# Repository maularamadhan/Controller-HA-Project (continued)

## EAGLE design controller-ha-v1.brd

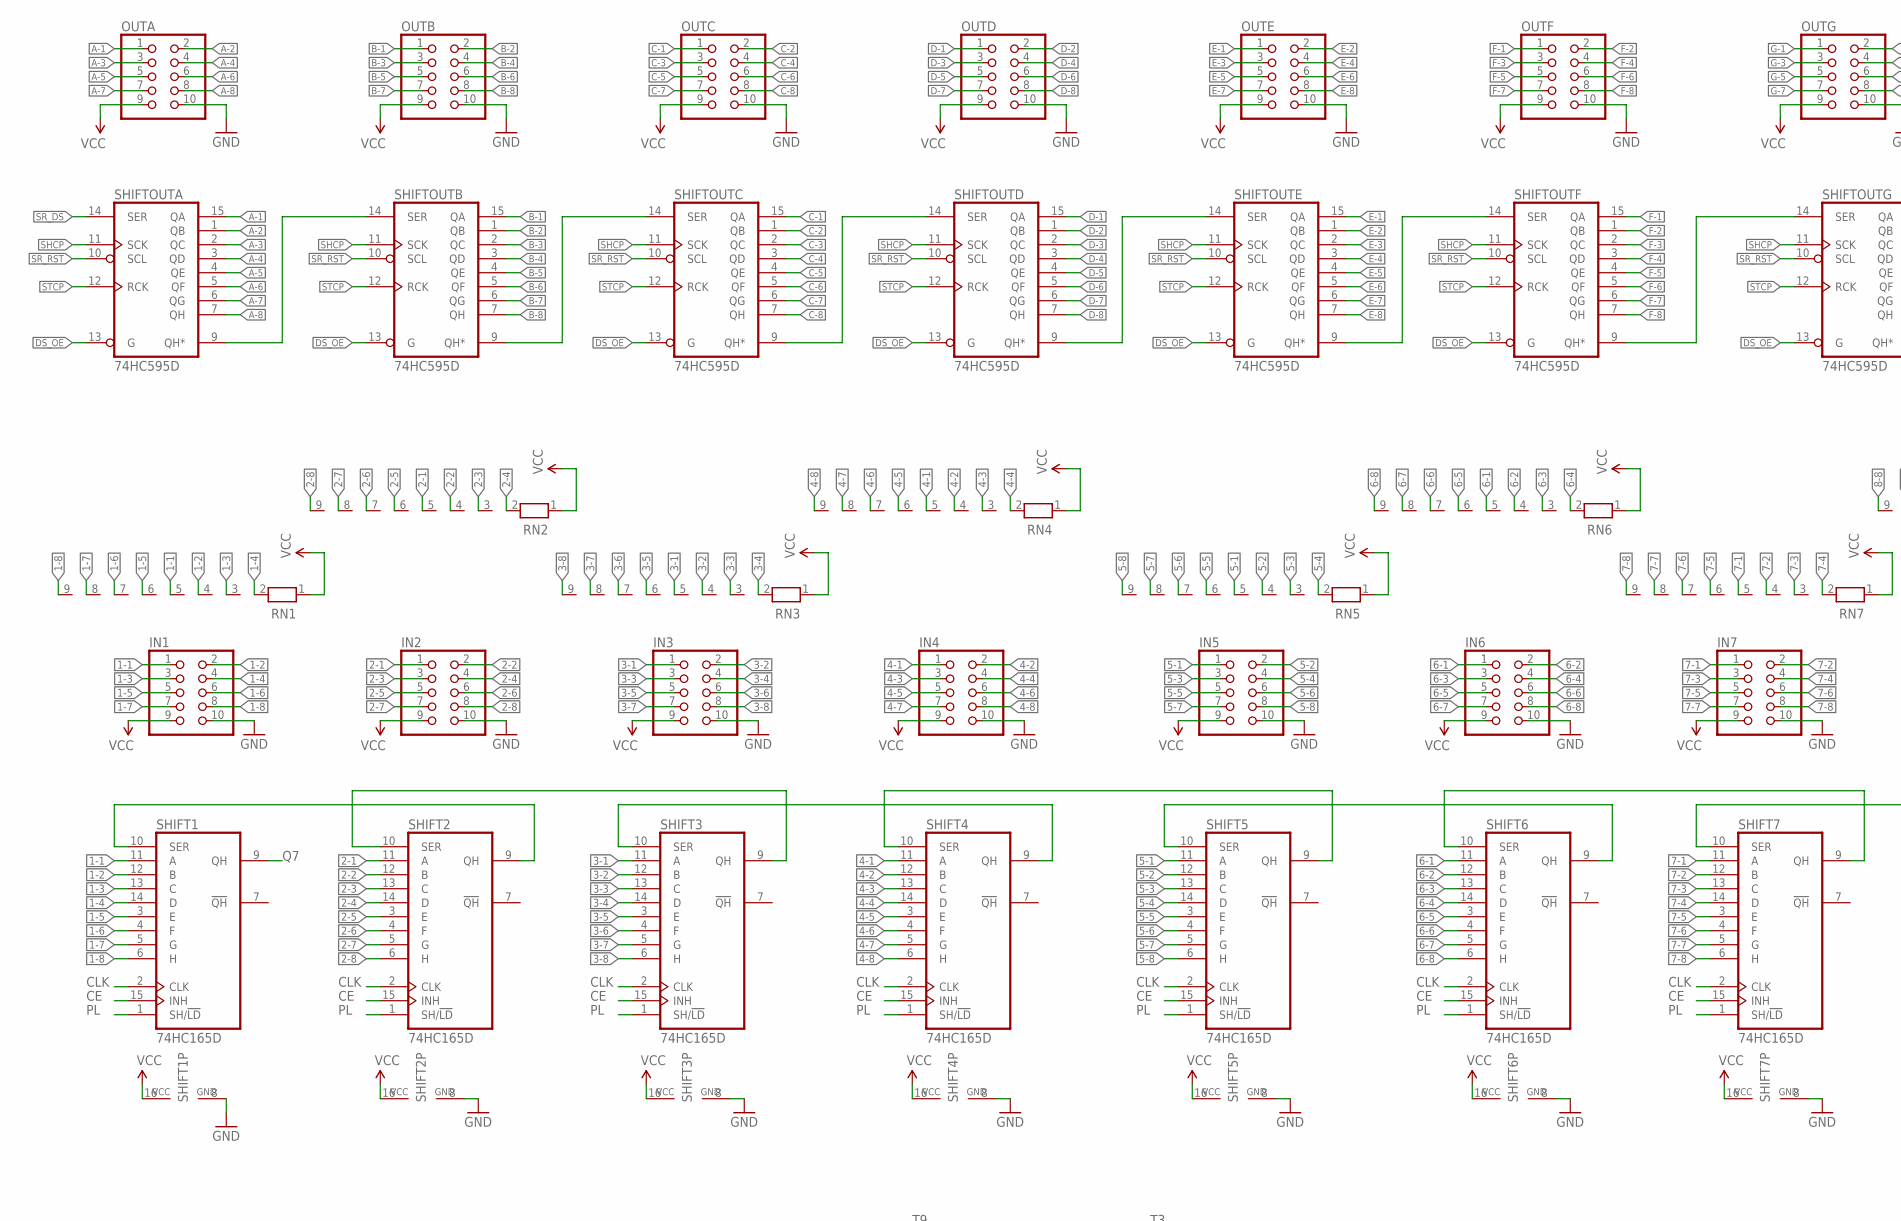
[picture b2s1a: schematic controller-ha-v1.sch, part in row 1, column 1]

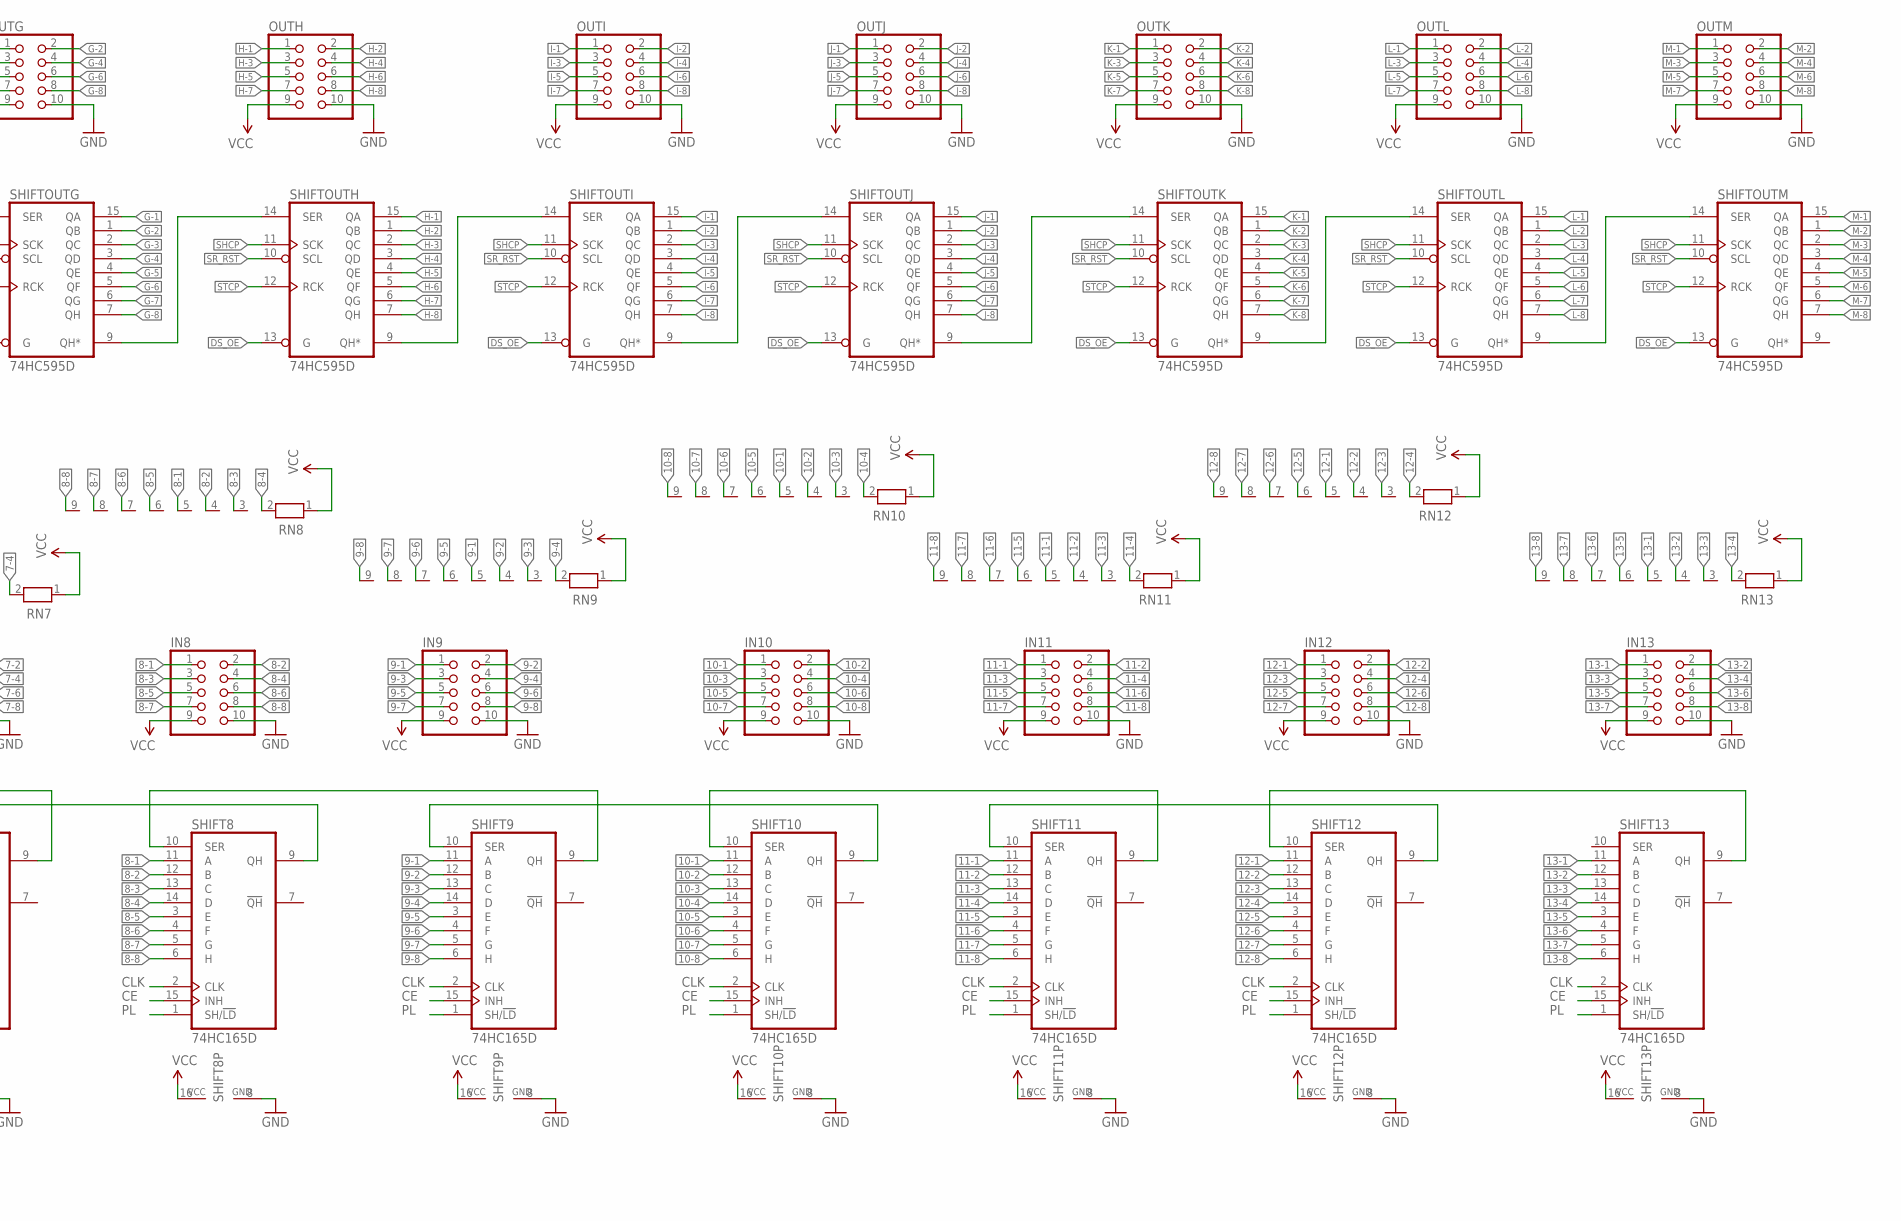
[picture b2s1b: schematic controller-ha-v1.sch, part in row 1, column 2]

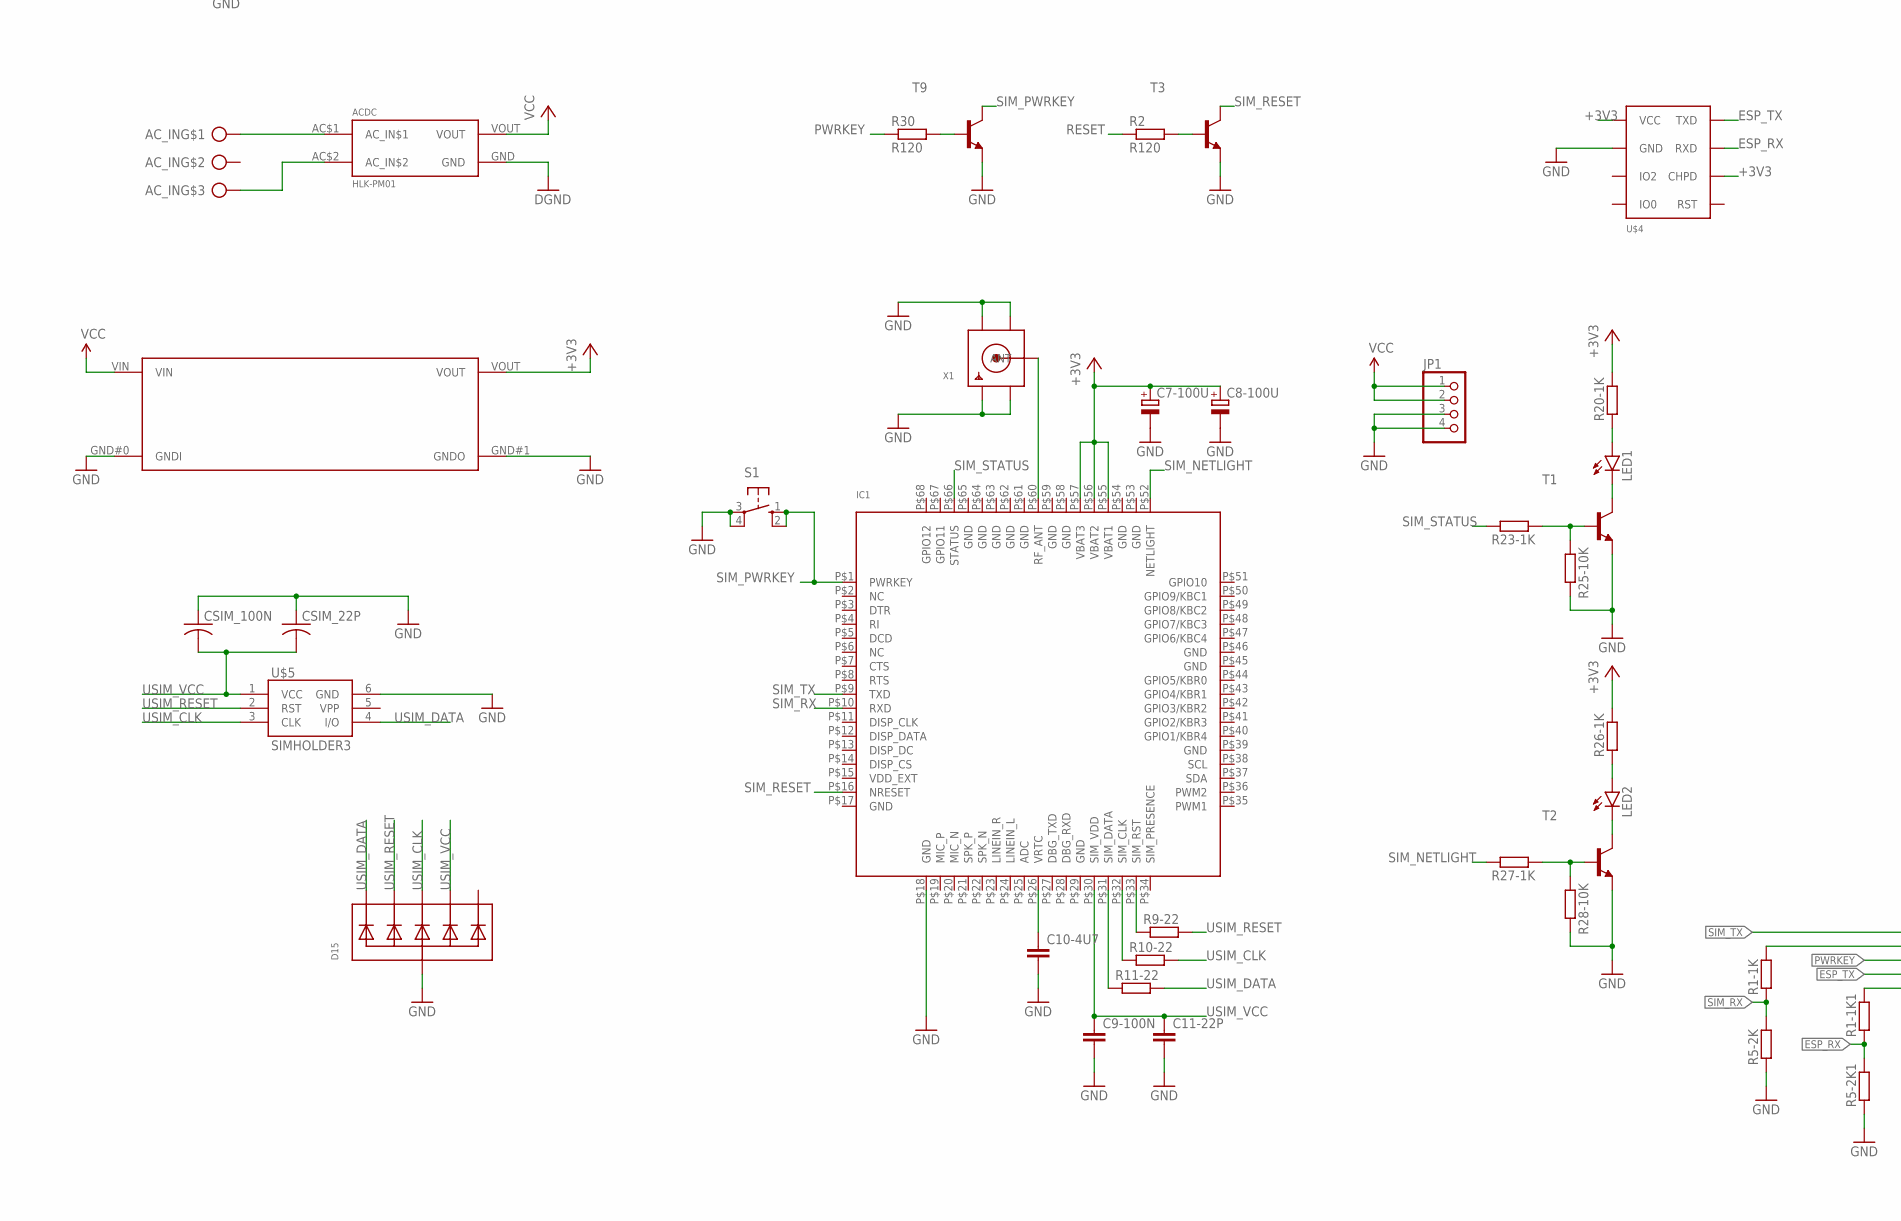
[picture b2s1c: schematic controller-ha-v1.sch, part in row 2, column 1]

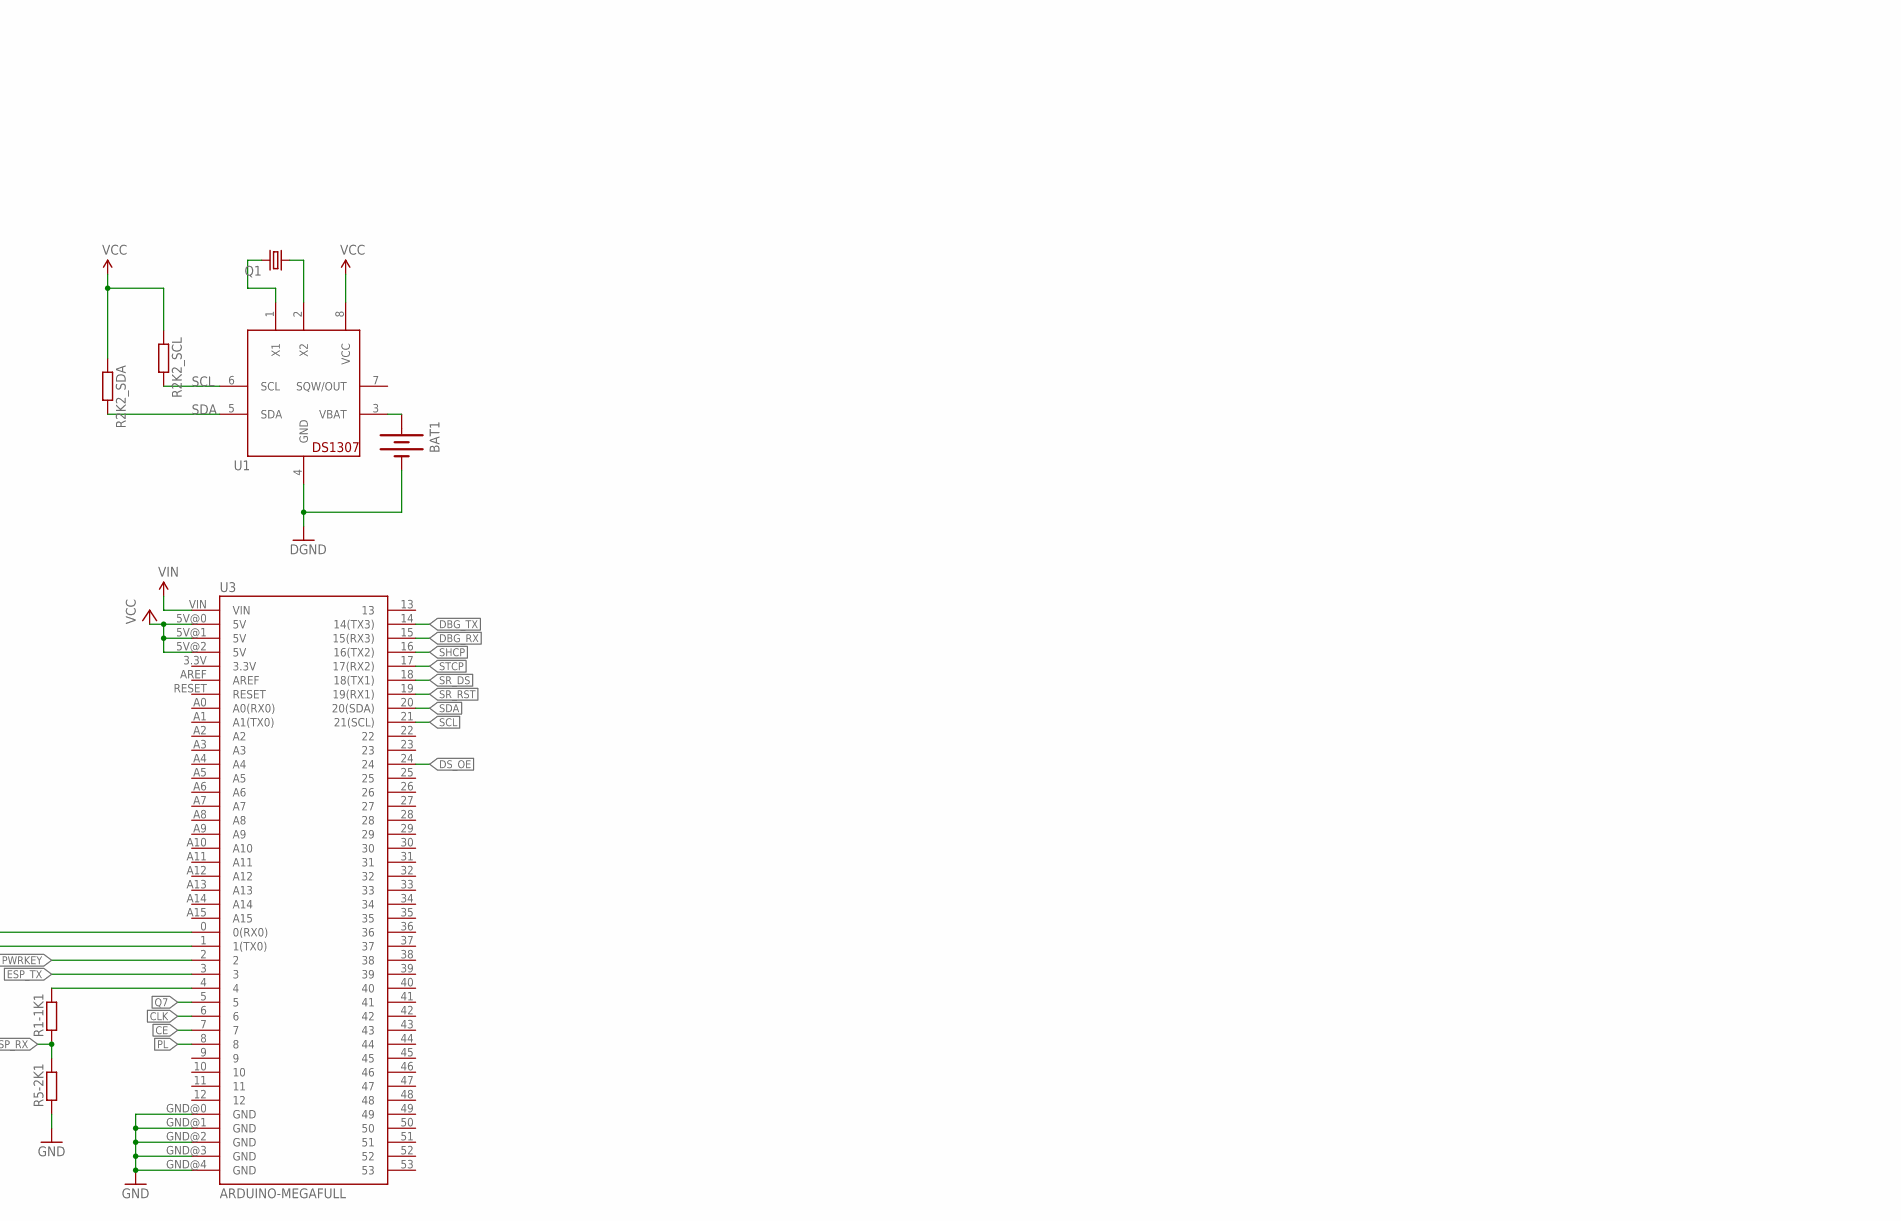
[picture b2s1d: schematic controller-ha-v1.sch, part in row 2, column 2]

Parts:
ACDC: HLK-PM01
AC_IN: AK3003
BAT1: BATTERY20PTH; BATTCOM_20MM_PTH
C7-100U, C8-100U: CPOL-EU153CLV-0605; 153CLV-0605
C9-100N, C10-4U7, C11-22P: C-EUC0603; C0603
CSIM_22P, CSIM_100N: C-USC0603K; C0603K
D15: TVSARRAY_5LANE; SOT363
IC1: GSM_SIM900_LITERAL; SIM900_SMT
IN1, IN2, IN3, IN4, IN5, IN6, IN7, IN8, IN9, IN10, IN11, IN12, IN13: PINHD-2X5; 2X05
JP1: PINHD-1X4; 1X04
LED1, LED2: LED-3MM-NO_SILK; LED3MM-NS
OUTA: PINHD-2X5; 2X05
OUTB: PINHD-2X5; 2X05
OUTC: PINHD-2X5; 2X05
OUTD: PINHD-2X5; 2X05
OUTE: PINHD-2X5; 2X05
OUTF: PINHD-2X5; 2X05
OUTG: PINHD-2X5; 2X05
OUTH: PINHD-2X5; 2X05
OUTI: PINHD-2X5; 2X05
OUTJ: PINHD-2X5; 2X05
OUTK: PINHD-2X5; 2X05
OUTL: PINHD-2X5; 2X05
OUTM: PINHD-2X5; 2X05
Q1: CRYSTALTC26H; TC26H
R1-1K, R1-1K1, R2K2_SCL, R2K2_SDA, R5-2K, R5-2K1, R9-22, R10-22, R11-22, R20-1K, R23-1K, R25-10K, R26-1K, R27-1K, R28-10K: R-EU_R0603; R0603
R2, R30: R120; M0805
RN1, RN2, RN3, RN4, RN5, RN6, RN7, RN8, RN9, RN10, RN11, RN12, RN13: RN08; RN-9
S1: 10-XX; B3F-10XX
SHIFT1, SHIFT2, SHIFT3, SHIFT4, SHIFT5, SHIFT6, SHIFT7, SHIFT8, SHIFT9, SHIFT10, SHIFT11, SHIFT12, SHIFT13: 74HC165D; SO16
SHIFTOUTA: 74HC595D; SO16
SHIFTOUTB: 74HC595D; SO16
SHIFTOUTC: 74HC595D; SO16
SHIFTOUTD: 74HC595D; SO16
SHIFTOUTE: 74HC595D; SO16
SHIFTOUTF: 74HC595D; SO16
SHIFTOUTG: 74HC595D; SO16
SHIFTOUTH: 74HC595D; SO16
SHIFTOUTI: 74HC595D; SO16
SHIFTOUTJ: 74HC595D; SO16
SHIFTOUTK: 74HC595D; SO16
SHIFTOUTL: 74HC595D; SO16
SHIFTOUTM: 74HC595D; SO16
T1, T2, T3, T9: MMBT2222ALT1-NPN-SOT23-BEC; SOT23-BEC
U1: DS1307; DIL08
U3: ARDUINO-MEGAFULL; ARDUINO_MEGA
U$2: DCDCMODULE
U$4: ESP8266
U$5: SIMHOLDER3
X1: SMACONNECTOR; SMA90_DIP

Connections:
1-1: IN1.1, RN1.5, SHIFT1.11 (A)
1-2: IN1.2, RN1.4, SHIFT1.12 (B)
1-3: IN1.3, RN1.3, SHIFT1.13 (C)
1-4: IN1.4, RN1.2, SHIFT1.14 (D)
1-5: IN1.5, RN1.6, SHIFT1.3 (E)
1-6: IN1.6, RN1.7, SHIFT1.4 (F)
1-7: IN1.7, RN1.8, SHIFT1.5 (G)
1-8: IN1.8, RN1.9, SHIFT1.6 (H)
2-1: IN2.1, RN2.5, SHIFT2.11 (A)
2-2: IN2.2, RN2.4, SHIFT2.12 (B)
2-3: IN2.3, RN2.3, SHIFT2.13 (C)
2-4: IN2.4, RN2.2, SHIFT2.14 (D)
2-5: IN2.5, RN2.6, SHIFT2.3 (E)
2-6: IN2.6, RN2.7, SHIFT2.4 (F)
2-7: IN2.7, RN2.8, SHIFT2.5 (G)
2-8: IN2.8, RN2.9, SHIFT2.6 (H)
3-1: IN3.1, RN3.5, SHIFT3.11 (A)
3-2: IN3.2, RN3.4, SHIFT3.12 (B)
3-3: IN3.3, RN3.3, SHIFT3.13 (C)
3-4: IN3.4, RN3.2, SHIFT3.14 (D)
3-5: IN3.5, RN3.6, SHIFT3.3 (E)
3-6: IN3.6, RN3.7, SHIFT3.4 (F)
3-7: IN3.7, RN3.8, SHIFT3.5 (G)
3-8: IN3.8, RN3.9, SHIFT3.6 (H)
4-1: IN4.1, RN4.5, SHIFT4.11 (A)
4-2: IN4.2, RN4.4, SHIFT4.12 (B)
4-3: IN4.3, RN4.3, SHIFT4.13 (C)
4-4: IN4.4, RN4.2, SHIFT4.14 (D)
4-5: IN4.5, RN4.6, SHIFT4.3 (E)
4-6: IN4.6, RN4.7, SHIFT4.4 (F)
4-7: IN4.7, RN4.8, SHIFT4.5 (G)
4-8: IN4.8, RN4.9, SHIFT4.6 (H)
5-1: IN5.1, RN5.5, SHIFT5.11 (A)
5-2: IN5.2, RN5.4, SHIFT5.12 (B)
5-3: IN5.3, RN5.3, SHIFT5.13 (C)
5-4: IN5.4, RN5.2, SHIFT5.14 (D)
5-5: IN5.5, RN5.6, SHIFT5.3 (E)
5-6: IN5.6, RN5.7, SHIFT5.4 (F)
5-7: IN5.7, RN5.8, SHIFT5.5 (G)
5-8: IN5.8, RN5.9, SHIFT5.6 (H)
6-1: IN6.1, RN6.5, SHIFT6.11 (A)
6-2: IN6.2, RN6.4, SHIFT6.12 (B)
6-3: IN6.3, RN6.3, SHIFT6.13 (C)
6-4: IN6.4, RN6.2, SHIFT6.14 (D)
6-5: IN6.5, RN6.6, SHIFT6.3 (E)
6-6: IN6.6, RN6.7, SHIFT6.4 (F)
6-7: IN6.7, RN6.8, SHIFT6.5 (G)
6-8: IN6.8, RN6.9, SHIFT6.6 (H)
7-1: IN7.1, RN7.5, SHIFT7.11 (A)
7-2: IN7.2, RN7.4, SHIFT7.12 (B)
7-3: IN7.3, RN7.3, SHIFT7.13 (C)
7-4: IN7.4, RN7.2, SHIFT7.14 (D)
7-5: IN7.5, RN7.6, SHIFT7.3 (E)
7-6: IN7.6, RN7.7, SHIFT7.4 (F)
7-7: IN7.7, RN7.8, SHIFT7.5 (G)
7-8: IN7.8, RN7.9, SHIFT7.6 (H)
8-1: IN8.1, RN8.5, SHIFT8.11 (A)
8-2: IN8.2, RN8.4, SHIFT8.12 (B)
8-3: IN8.3, RN8.3, SHIFT8.13 (C)
8-4: IN8.4, RN8.2, SHIFT8.14 (D)
8-5: IN8.5, RN8.6, SHIFT8.3 (E)
8-6: IN8.6, RN8.7, SHIFT8.4 (F)
8-7: IN8.7, RN8.8, SHIFT8.5 (G)
8-8: IN8.8, RN8.9, SHIFT8.6 (H)
9-1: IN9.1, RN9.5, SHIFT9.11 (A)
9-2: IN9.2, RN9.4, SHIFT9.12 (B)
9-3: IN9.3, RN9.3, SHIFT9.13 (C)
9-4: IN9.4, RN9.2, SHIFT9.14 (D)
9-5: IN9.5, RN9.6, SHIFT9.3 (E)
9-6: IN9.6, RN9.7, SHIFT9.4 (F)
9-7: IN9.7, RN9.8, SHIFT9.5 (G)
9-8: IN9.8, RN9.9, SHIFT9.6 (H)
10-1: IN10.1, RN10.5, SHIFT10.11 (A)
10-2: IN10.2, RN10.4, SHIFT10.12 (B)
10-3: IN10.3, RN10.3, SHIFT10.13 (C)
10-4: IN10.4, RN10.2, SHIFT10.14 (D)
10-5: IN10.5, RN10.6, SHIFT10.3 (E)
10-6: IN10.6, RN10.7, SHIFT10.4 (F)
10-7: IN10.7, RN10.8, SHIFT10.5 (G)
10-8: IN10.8, RN10.9, SHIFT10.6 (H)
11-1: IN11.1, RN11.5, SHIFT11.11 (A)
11-2: IN11.2, RN11.4, SHIFT11.12 (B)
11-3: IN11.3, RN11.3, SHIFT11.13 (C)
11-4: IN11.4, RN11.2, SHIFT11.14 (D)
11-5: IN11.5, RN11.6, SHIFT11.3 (E)
11-6: IN11.6, RN11.7, SHIFT11.4 (F)
11-7: IN11.7, RN11.8, SHIFT11.5 (G)
11-8: IN11.8, RN11.9, SHIFT11.6 (H)
12-1: IN12.1, RN12.5, SHIFT12.11 (A)
12-2: IN12.2, RN12.4, SHIFT12.12 (B)
12-3: IN12.3, RN12.3, SHIFT12.13 (C)
12-4: IN12.4, RN12.2, SHIFT12.14 (D)
12-5: IN12.5, RN12.6, SHIFT12.3 (E)
12-6: IN12.6, RN12.7, SHIFT12.4 (F)
12-7: IN12.7, RN12.8, SHIFT12.5 (G)
12-8: IN12.8, RN12.9, SHIFT12.6 (H)
13-1: IN13.1, RN13.5, SHIFT13.11 (A)
13-2: IN13.2, RN13.4, SHIFT13.12 (B)
13-3: IN13.3, RN13.3, SHIFT13.13 (C)
13-4: IN13.4, RN13.2, SHIFT13.14 (D)
13-5: IN13.5, RN13.6, SHIFT13.3 (E)
13-6: IN13.6, RN13.7, SHIFT13.4 (F)
13-7: IN13.7, RN13.8, SHIFT13.5 (G)
13-8: IN13.8, RN13.9, SHIFT13.6 (H)
+3V3: C7-100U.+, C8-100U.+, IC1.P$55 (VBAT1), IC1.P$56 (VBAT2), IC1.P$57 (VBAT3), R20-1K.2, R26-1K.2, U$2.VOUT, U$4.CHPD, U$4.VCC
A-1: OUTA.1, SHIFTOUTA.15 (QA)
A-2: OUTA.2, SHIFTOUTA.1 (QB)
A-3: OUTA.3, SHIFTOUTA.2 (QC)
A-4: OUTA.4, SHIFTOUTA.3 (QD)
A-5: OUTA.5, SHIFTOUTA.4 (QE)
A-6: OUTA.6, SHIFTOUTA.5 (QF)
A-7: OUTA.7, SHIFTOUTA.6 (QG)
A-8: OUTA.8, SHIFTOUTA.7 (QH)
B-1: OUTB.1, SHIFTOUTB.15 (QA)
B-2: OUTB.2, SHIFTOUTB.1 (QB)
B-3: OUTB.3, SHIFTOUTB.2 (QC)
B-4: OUTB.4, SHIFTOUTB.3 (QD)
B-5: OUTB.5, SHIFTOUTB.4 (QE)
B-6: OUTB.6, SHIFTOUTB.5 (QF)
B-7: OUTB.7, SHIFTOUTB.6 (QG)
B-8: OUTB.8, SHIFTOUTB.7 (QH)
C-1: OUTC.1, SHIFTOUTC.15 (QA)
C-2: OUTC.2, SHIFTOUTC.1 (QB)
C-3: OUTC.3, SHIFTOUTC.2 (QC)
C-4: OUTC.4, SHIFTOUTC.3 (QD)
C-5: OUTC.5, SHIFTOUTC.4 (QE)
C-6: OUTC.6, SHIFTOUTC.5 (QF)
C-7: OUTC.7, SHIFTOUTC.6 (QG)
C-8: OUTC.8, SHIFTOUTC.7 (QH)
CE: SHIFT1.15 (INH), SHIFT2.15 (INH), SHIFT3.15 (INH), SHIFT4.15 (INH), SHIFT5.15 (INH), SHIFT6.15 (INH), SHIFT7.15 (INH), SHIFT8.15 (INH), SHIFT9.15 (INH), SHIFT10.15 (INH), SHIFT11.15 (INH), SHIFT12.15 (INH), SHIFT13.15 (INH), U3.7
CLK: SHIFT1.2 (CLK), SHIFT2.2 (CLK), SHIFT3.2 (CLK), SHIFT4.2 (CLK), SHIFT5.2 (CLK), SHIFT6.2 (CLK), SHIFT7.2 (CLK), SHIFT8.2 (CLK), SHIFT9.2 (CLK), SHIFT10.2 (CLK), SHIFT11.2 (CLK), SHIFT12.2 (CLK), SHIFT13.2 (CLK), U3.6
D-1: OUTD.1, SHIFTOUTD.15 (QA)
D-2: OUTD.2, SHIFTOUTD.1 (QB)
D-3: OUTD.3, SHIFTOUTD.2 (QC)
D-4: OUTD.4, SHIFTOUTD.3 (QD)
D-5: OUTD.5, SHIFTOUTD.4 (QE)
D-6: OUTD.6, SHIFTOUTD.5 (QF)
D-7: OUTD.7, SHIFTOUTD.6 (QG)
D-8: OUTD.8, SHIFTOUTD.7 (QH)
DBG_RX: U3.15 (15(RX3))
DBG_TX: U3.14 (14(TX3))
DS_OE: SHIFTOUTA.13 (G), SHIFTOUTB.13 (G), SHIFTOUTC.13 (G), SHIFTOUTD.13 (G), SHIFTOUTE.13 (G), SHIFTOUTF.13 (G), SHIFTOUTG.13 (G), SHIFTOUTH.13 (G), SHIFTOUTI.13 (G), SHIFTOUTJ.13 (G), SHIFTOUTK.13 (G), SHIFTOUTL.13 (G), SHIFTOUTM.13 (G), U3.24
E-1: OUTE.1, SHIFTOUTE.15 (QA)
E-2: OUTE.2, SHIFTOUTE.1 (QB)
E-3: OUTE.3, SHIFTOUTE.2 (QC)
E-4: OUTE.4, SHIFTOUTE.3 (QD)
E-5: OUTE.5, SHIFTOUTE.4 (QE)
E-6: OUTE.6, SHIFTOUTE.5 (QF)
E-7: OUTE.7, SHIFTOUTE.6 (QG)
E-8: OUTE.8, SHIFTOUTE.7 (QH)
ESP_RX: R1-1K1.1, R5-2K1.2, U$4.RXD
ESP_TX: U3.3, U$4.TXD
F-1: OUTF.1, SHIFTOUTF.15 (QA)
F-2: OUTF.2, SHIFTOUTF.1 (QB)
F-3: OUTF.3, SHIFTOUTF.2 (QC)
F-4: OUTF.4, SHIFTOUTF.3 (QD)
F-5: OUTF.5, SHIFTOUTF.4 (QE)
F-6: OUTF.6, SHIFTOUTF.5 (QF)
F-7: OUTF.7, SHIFTOUTF.6 (QG)
F-8: OUTF.8, SHIFTOUTF.7 (QH)
G-1: OUTG.1, SHIFTOUTG.15 (QA)
G-2: OUTG.2, SHIFTOUTG.1 (QB)
G-3: OUTG.3, SHIFTOUTG.2 (QC)
G-4: OUTG.4, SHIFTOUTG.3 (QD)
G-5: OUTG.5, SHIFTOUTG.4 (QE)
G-6: OUTG.6, SHIFTOUTG.5 (QF)
G-7: OUTG.7, SHIFTOUTG.6 (QG)
G-8: OUTG.8, SHIFTOUTG.7 (QH)
GND: ACDC.GND, BAT1.2 (-), C7-100U.-, C8-100U.-, C9-100N.2, C10-4U7.2, C11-22P.2, CSIM_22P.1, CSIM_100N.1, D15.2 (A), IC1.P$17 (GND), IC1.P$18 (GND), IC1.P$29 (GND), IC1.P$39 (GND), IC1.P$45 (GND), IC1.P$46 (GND), IC1.P$53 (GND), IC1.P$54 (GND), IC1.P$58 (GND), IC1.P$59 (GND), IC1.P$61 (GND), IC1.P$62 (GND), IC1.P$63 (GND), IC1.P$64 (GND), IC1.P$65 (GND), IN1.10, IN2.10, IN3.10, IN4.10, IN5.10, IN6.10, IN7.10, IN8.10, IN9.10, IN10.10, IN11.10, IN12.10, IN13.10, JP1.3, JP1.4, OUTA.10, OUTB.10, OUTC.10, OUTD.10, OUTE.10, OUTF.10, OUTG.10, OUTH.10, OUTI.10, OUTJ.10, OUTK.10, OUTL.10, OUTM.10, R5-2K.1, R5-2K1.1, R25-10K.2, R28-10K.2, S1.3, S1.4 (P1), SHIFT1.8 (GND), SHIFT2.8 (GND), SHIFT3.8 (GND), SHIFT4.8 (GND), SHIFT5.8 (GND), SHIFT6.8 (GND), SHIFT7.8 (GND), SHIFT8.8 (GND), SHIFT9.8 (GND), SHIFT10.8 (GND), SHIFT11.8 (GND), SHIFT12.8 (GND), SHIFT13.8 (GND), SHIFTOUTA.8 (GND), SHIFTOUTB.8 (GND), SHIFTOUTC.8 (GND), SHIFTOUTD.8 (GND), SHIFTOUTE.8 (GND), SHIFTOUTF.8 (GND), SHIFTOUTG.8 (GND), SHIFTOUTH.8 (GND), SHIFTOUTI.8 (GND), SHIFTOUTJ.8 (GND), SHIFTOUTK.8 (GND), SHIFTOUTL.8 (GND), SHIFTOUTM.8 (GND), T1.E, T2.E, T3.E, T9.E, U1.4 (GND), U3.GND@0 (GND), U3.GND@1 (GND), U3.GND@2 (GND), U3.GND@3 (GND), U3.GND@4 (GND), U$2.GND#0 (GNDI), U$2.GND#1 (GNDO), U$4.GND, U$5.6 (GND), X1.GND1, X1.GND2, X1.GND3, X1.GND4
GPIO11: IC1.P$67 (GPIO11)
GPIO12: IC1.P$68 (GPIO12)
H-1: OUTH.1, SHIFTOUTH.15 (QA)
H-2: OUTH.2, SHIFTOUTH.1 (QB)
H-3: OUTH.3, SHIFTOUTH.2 (QC)
H-4: OUTH.4, SHIFTOUTH.3 (QD)
H-5: OUTH.5, SHIFTOUTH.4 (QE)
H-6: OUTH.6, SHIFTOUTH.5 (QF)
H-7: OUTH.7, SHIFTOUTH.6 (QG)
H-8: OUTH.8, SHIFTOUTH.7 (QH)
I-1: OUTI.1, SHIFTOUTI.15 (QA)
I-2: OUTI.2, SHIFTOUTI.1 (QB)
I-3: OUTI.3, SHIFTOUTI.2 (QC)
I-4: OUTI.4, SHIFTOUTI.3 (QD)
I-5: OUTI.5, SHIFTOUTI.4 (QE)
I-6: OUTI.6, SHIFTOUTI.5 (QF)
I-7: OUTI.7, SHIFTOUTI.6 (QG)
I-8: OUTI.8, SHIFTOUTI.7 (QH)
J-1: OUTJ.1, SHIFTOUTJ.15 (QA)
J-2: OUTJ.2, SHIFTOUTJ.1 (QB)
J-3: OUTJ.3, SHIFTOUTJ.2 (QC)
J-4: OUTJ.4, SHIFTOUTJ.3 (QD)
J-5: OUTJ.5, SHIFTOUTJ.4 (QE)
J-6: OUTJ.6, SHIFTOUTJ.5 (QF)
J-7: OUTJ.7, SHIFTOUTJ.6 (QG)
J-8: OUTJ.8, SHIFTOUTJ.7 (QH)
K-1: OUTK.1, SHIFTOUTK.15 (QA)
K-2: OUTK.2, SHIFTOUTK.1 (QB)
K-3: OUTK.3, SHIFTOUTK.2 (QC)
K-4: OUTK.4, SHIFTOUTK.3 (QD)
K-5: OUTK.5, SHIFTOUTK.4 (QE)
K-6: OUTK.6, SHIFTOUTK.5 (QF)
K-7: OUTK.7, SHIFTOUTK.6 (QG)
K-8: OUTK.8, SHIFTOUTK.7 (QH)
L-1: OUTL.1, SHIFTOUTL.15 (QA)
L-2: OUTL.2, SHIFTOUTL.1 (QB)
L-3: OUTL.3, SHIFTOUTL.2 (QC)
L-4: OUTL.4, SHIFTOUTL.3 (QD)
L-5: OUTL.5, SHIFTOUTL.4 (QE)
L-6: OUTL.6, SHIFTOUTL.5 (QF)
L-7: OUTL.7, SHIFTOUTL.6 (QG)
L-8: OUTL.8, SHIFTOUTL.7 (QH)
M-1: OUTM.1, SHIFTOUTM.15 (QA)
M-2: OUTM.2, SHIFTOUTM.1 (QB)
M-3: OUTM.3, SHIFTOUTM.2 (QC)
M-4: OUTM.4, SHIFTOUTM.3 (QD)
M-5: OUTM.5, SHIFTOUTM.4 (QE)
M-6: OUTM.6, SHIFTOUTM.5 (QF)
M-7: OUTM.7, SHIFTOUTM.6 (QG)
M-8: OUTM.8, SHIFTOUTM.7 (QH)
unnamed: R1-1K.2, U3.1 (1(TX0))
unnamed: IC1.P$31 (SIM_DATA), R11-22.1
unnamed: IC1.P$32 (SIM_CLK), R10-22.1
unnamed: IC1.P$33 (SIM_RST), R9-22.1
unnamed: C10-4U7.1, IC1.P$26 (VRTC)
unnamed: IC1.P$60 (RF_ANT), X1.ANTENNA (ANT)
unnamed: ACDC.AC$1 (AC_IN$1), AC_IN.1
unnamed: LED1.A, R20-1K.1
unnamed: LED1.K (C), T1.C
unnamed: R23-1K.1, R25-10K.1, T1.B
unnamed: LED2.A, R26-1K.1
unnamed: LED2.K (C), T2.C
unnamed: R27-1K.1, R28-10K.1, T2.B
unnamed: R30.2, T9.B
unnamed: R2.2, T3.B
unnamed: Q1.1, U1.2 (X2)
unnamed: ACDC.AC$2 (AC_IN$2), AC_IN.3
unnamed: SHIFT2.10 (SER), SHIFT3.9 (QH)
unnamed: Q1.2, U1.1 (X1)
unnamed: R1-1K1.2, U3.4
unnamed: SHIFT3.10 (SER), SHIFT4.9 (QH)
unnamed: SHIFT4.10 (SER), SHIFT5.9 (QH)
unnamed: BAT1.1 (+), U1.3 (VBAT)
unnamed: SHIFT5.10 (SER), SHIFT6.9 (QH)
unnamed: SHIFT7.10 (SER), SHIFT8.9 (QH)
unnamed: SHIFTOUTA.9 (QH*), SHIFTOUTB.14 (SER)
unnamed: SHIFT8.10 (SER), SHIFT9.9 (QH)
unnamed: SHIFT12.10 (SER), SHIFT13.9 (QH)
unnamed: SHIFT11.10 (SER), SHIFT12.9 (QH)
unnamed: SHIFT10.10 (SER), SHIFT11.9 (QH)
unnamed: SHIFTOUTC.9 (QH*), SHIFTOUTD.14 (SER)
unnamed: SHIFTOUTE.9 (QH*), SHIFTOUTF.14 (SER)
unnamed: SHIFTOUTG.9 (QH*), SHIFTOUTH.14 (SER)
unnamed: SHIFTOUTI.9 (QH*), SHIFTOUTJ.14 (SER)
unnamed: SHIFTOUTK.9 (QH*), SHIFTOUTL.14 (SER)
unnamed: SHIFT6.10 (SER), SHIFT7.9 (QH)
unnamed: SHIFTOUTB.9 (QH*), SHIFTOUTC.14 (SER)
unnamed: SHIFTOUTD.9 (QH*), SHIFTOUTE.14 (SER)
unnamed: SHIFTOUTF.9 (QH*), SHIFTOUTG.14 (SER)
unnamed: SHIFTOUTH.9 (QH*), SHIFTOUTI.14 (SER)
unnamed: SHIFTOUTJ.9 (QH*), SHIFTOUTK.14 (SER)
unnamed: SHIFTOUTL.9 (QH*), SHIFTOUTM.14 (SER)
unnamed: SHIFT1.10 (SER), SHIFT2.9 (QH)
unnamed: SHIFT9.10 (SER), SHIFT10.9 (QH)
PL: SHIFT1.1 (SH/!LD), SHIFT2.1 (SH/!LD), SHIFT3.1 (SH/!LD), SHIFT4.1 (SH/!LD), SHIFT5.1 (SH/!LD), SHIFT6.1 (SH/!LD), SHIFT7.1 (SH/!LD), SHIFT8.1 (SH/!LD), SHIFT9.1 (SH/!LD), SHIFT10.1 (SH/!LD), SHIFT11.1 (SH/!LD), SHIFT12.1 (SH/!LD), SHIFT13.1 (SH/!LD), U3.8
PWRKEY: R30.1, U3.2
Q7: SHIFT1.9 (QH), U3.5
RESET: R2.1
SCL: R2K2_SCL.2, U1.6 (SCL), U3.21 (21(SCL))
SDA: R2K2_SDA.2, U1.5 (SDA), U3.20 (20(SDA))
SHCP: SHIFTOUTA.11 (SCK), SHIFTOUTB.11 (SCK), SHIFTOUTC.11 (SCK), SHIFTOUTD.11 (SCK), SHIFTOUTE.11 (SCK), SHIFTOUTF.11 (SCK), SHIFTOUTG.11 (SCK), SHIFTOUTH.11 (SCK), SHIFTOUTI.11 (SCK), SHIFTOUTJ.11 (SCK), SHIFTOUTK.11 (SCK), SHIFTOUTL.11 (SCK), SHIFTOUTM.11 (SCK), U3.16 (16(TX2))
SIM_NETLIGHT: IC1.P$52 (NETLIGHT), R27-1K.2
SIM_PWRKEY: IC1.P$1 (PWRKEY), S1.1 (S), S1.2 (S1), T9.C
SIM_RESET: IC1.P$16 (NRESET), T3.C
SIM_RX: IC1.P$10 (RXD), R1-1K.1, R5-2K.2
SIM_STATUS: IC1.P$66 (STATUS), R23-1K.2
SIM_TX: IC1.P$9 (TXD), U3.0 (0(RX0))
SR_DS: SHIFTOUTA.14 (SER), U3.18 (18(TX1))
SR_RST: SHIFTOUTA.10 (SCL), SHIFTOUTB.10 (SCL), SHIFTOUTC.10 (SCL), SHIFTOUTD.10 (SCL), SHIFTOUTE.10 (SCL), SHIFTOUTF.10 (SCL), SHIFTOUTG.10 (SCL), SHIFTOUTH.10 (SCL), SHIFTOUTI.10 (SCL), SHIFTOUTJ.10 (SCL), SHIFTOUTK.10 (SCL), SHIFTOUTL.10 (SCL), SHIFTOUTM.10 (SCL), U3.19 (19(RX1))
STCP: SHIFTOUTA.12 (RCK), SHIFTOUTB.12 (RCK), SHIFTOUTC.12 (RCK), SHIFTOUTD.12 (RCK), SHIFTOUTE.12 (RCK), SHIFTOUTF.12 (RCK), SHIFTOUTG.12 (RCK), SHIFTOUTH.12 (RCK), SHIFTOUTI.12 (RCK), SHIFTOUTJ.12 (RCK), SHIFTOUTK.12 (RCK), SHIFTOUTL.12 (RCK), SHIFTOUTM.12 (RCK), U3.17 (17(RX2))
USIM_CLK: D15.4 (C3), R10-22.2, U$5.3 (CLK)
USIM_DATA: D15.1 (C1), R11-22.2, U$5.4 (I/O)
USIM_RESET: D15.3 (C2), R9-22.2, U$5.2 (RST)
USIM_VCC: C9-100N.1, C11-22P.1, CSIM_22P.2, CSIM_100N.2, D15.5 (C4), IC1.P$30 (SIM_VDD), U$5.1 (VCC)
VCC: ACDC.VOUT, IN1.9, IN2.9, IN3.9, IN4.9, IN5.9, IN6.9, IN7.9, IN8.9, IN9.9, IN10.9, IN11.9, IN12.9, IN13.9, JP1.1, JP1.2, OUTA.9, OUTB.9, OUTC.9, OUTD.9, OUTE.9, OUTF.9, OUTG.9, OUTH.9, OUTI.9, OUTJ.9, OUTK.9, OUTL.9, OUTM.9, R2K2_SCL.1, R2K2_SDA.1, RN1.1, RN2.1, RN3.1, RN4.1, RN5.1, RN6.1, RN7.1, RN8.1, RN9.1, RN10.1, RN11.1, RN12.1, RN13.1, SHIFT1.16 (VCC), SHIFT2.16 (VCC), SHIFT3.16 (VCC), SHIFT4.16 (VCC), SHIFT5.16 (VCC), SHIFT6.16 (VCC), SHIFT7.16 (VCC), SHIFT8.16 (VCC), SHIFT9.16 (VCC), SHIFT10.16 (VCC), SHIFT11.16 (VCC), SHIFT12.16 (VCC), SHIFT13.16 (VCC), SHIFTOUTA.16 (VCC), SHIFTOUTB.16 (VCC), SHIFTOUTC.16 (VCC), SHIFTOUTD.16 (VCC), SHIFTOUTE.16 (VCC), SHIFTOUTF.16 (VCC), SHIFTOUTG.16 (VCC), SHIFTOUTH.16 (VCC), SHIFTOUTI.16 (VCC), SHIFTOUTJ.16 (VCC), SHIFTOUTK.16 (VCC), SHIFTOUTL.16 (VCC), SHIFTOUTM.16 (VCC), U1.8 (VCC), U3.5V@0 (5V), U3.5V@1 (5V), U3.5V@2 (5V), U$2.VIN
VIN: U3.VIN

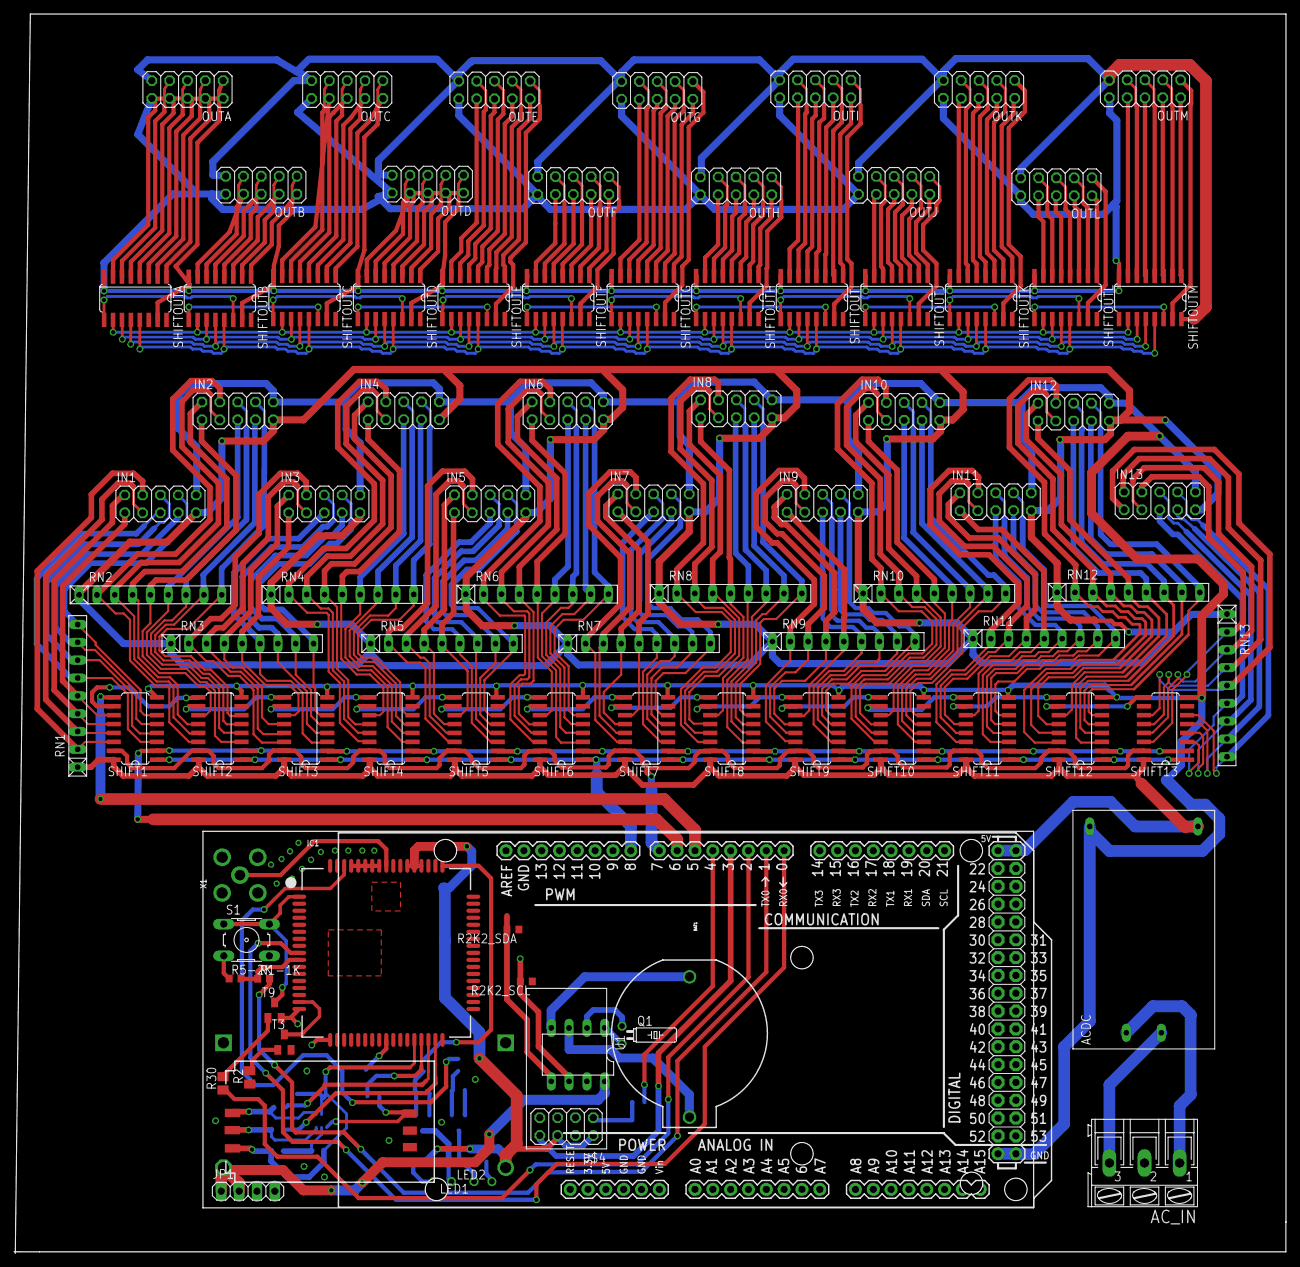
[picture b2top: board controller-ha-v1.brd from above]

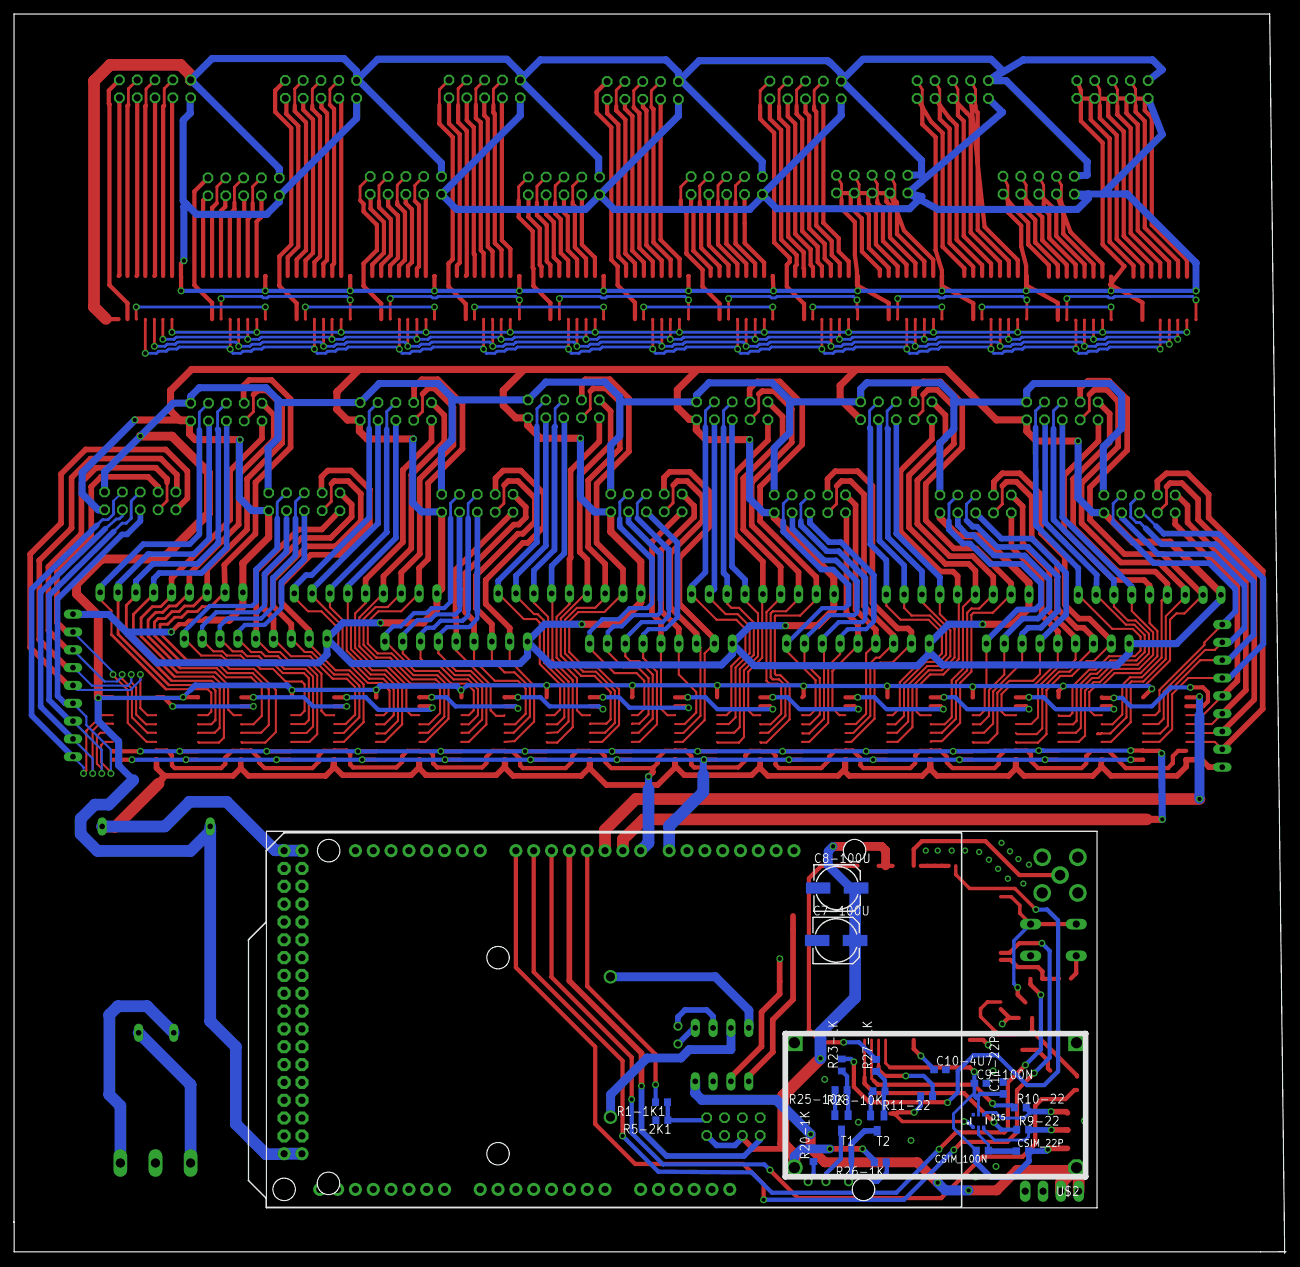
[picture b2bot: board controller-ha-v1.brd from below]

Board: 2 copper layers, 181.2 x 176.6 mm, 109 parts (22 on the bottom side), 279 nets.
